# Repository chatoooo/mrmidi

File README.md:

# Mr. MIDI
MIDI interface for MiSTer FPGA with ADC to mix music with SFX and output over HDMI/audio jack. The design aims to DIY assembly and uses only thru-hole parts.

## Principe
Thanks to MT-32pi - MiSTer compatibility, there are MIDI out and I2S signals on the user port on the Analog/Digital IO board. 
MT-32pi gets the MIDI data and produces I2S data, that are mixed with SFX output from the emulated sound card.
To get the same result with a real MIDI synth, we need a line driver to get 3.3V logic of the MiSTer to 5V levels of the MIDI interface 
and ADC with I2S output to digitalize analog audio output from the synth. Connection with MiSTer is though USB 3.0 cable (male-male), the same one as for MT-32pi hat.

## Manufacture
The PCB is optimzied for JLCPCB. Use the gerber files from the latest release. 

## BOM

|Id |Value|Note|
|---|-----|----|
|R1 |180R 0207|For LED D1|
|R2 |180R 0207|For LED D2|
|R3 |4K7 0207 |signal for Q1|
|R4 |220R 0207|MIDI interface|
|R5 |220R 0207|MIDI interface|
|C1 |100nF 5mm|bypass|
|Q1 |BS170_D26Z|for driving LED D2|
|D1 |3mm 20mA 2V|power LED|
|D2 |3mm 20mA 2V|activity LED|
|U1 |SN74HCT14N||
|J1 |CONNFLY DS1095-05-LNR0|USB 3.0 A Female|
|J2 |DIN 5 Female|https://www.mouser.co.uk/ProductDetail/490-SDS-50J, or similar, almost all DIN5-180 connectors have the same footprint|
|A1 |PCM1808|ADC module|

A1 is PCM1808 module abvailable on Aliexpress: <https://www.aliexpress.com/item/1005006141604047.html>. 
There is another PCM1808 module, usually purple which is not compatible with this project.
The module can be soldered directly or using female pin headers (1x2, 1x5, 1x3).

## Bootstraping the module
The PCM1808 module needs to be set to master, I2S-24 bits, 48000Hz.
| OP1 | OP2 | OP3 |
|:---:|:---:|:---:|
|open |short|open |

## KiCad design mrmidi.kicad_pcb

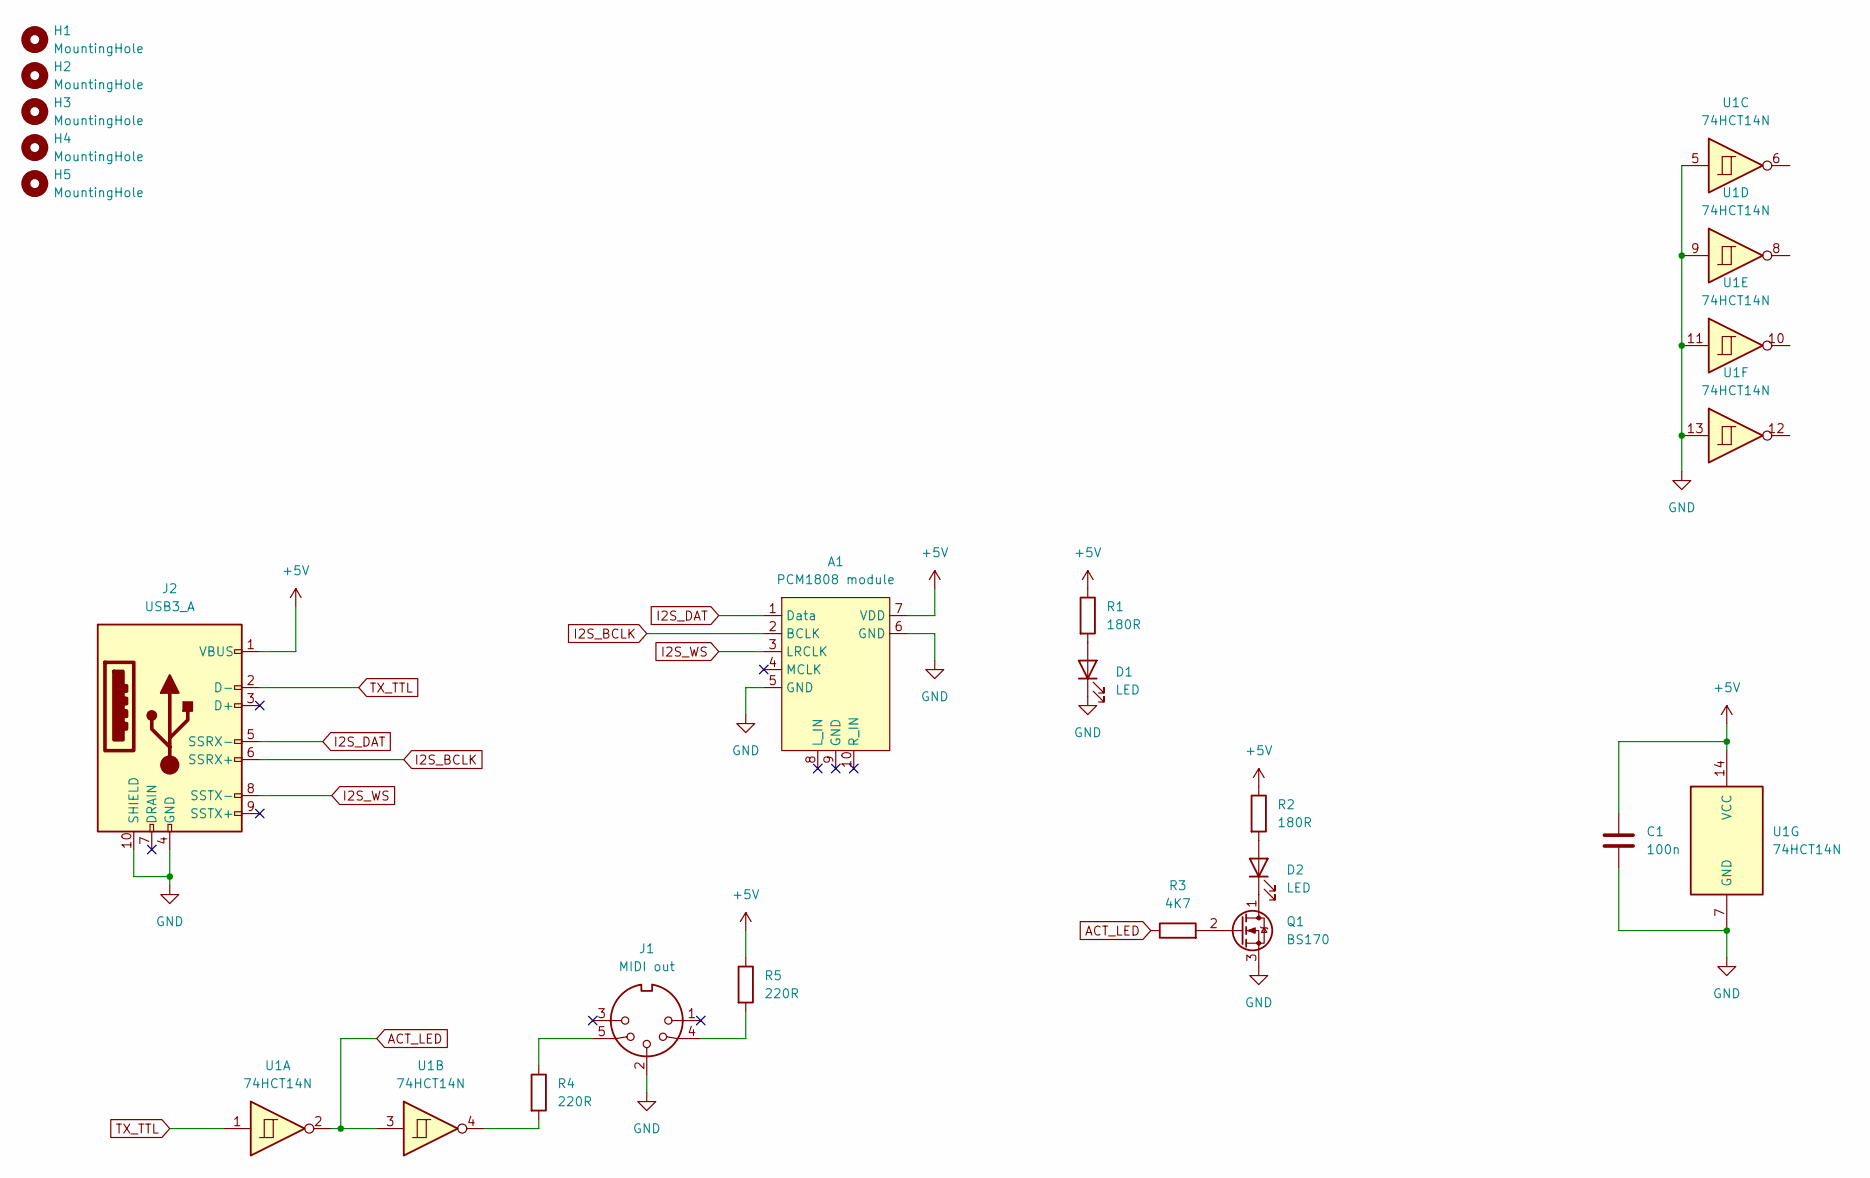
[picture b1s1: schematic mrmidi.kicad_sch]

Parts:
A1: PCM1808 module; PCM1808_module_upside_down
C1: 100n; C_Disc_D4.3mm_W1.9mm_P5.00mm
D1, D2: LED; LED_D3.0mm
H1, H2, H3, H4: MountingHole; MountingHole_3mm
H5: MountingHole; MountingHole_5mm
J1: MIDI out; DIN-5-Variable
J2: USB3_A; USB3_A_Confly_1095-05
Q1: BS170; TO-92L_Inline_Wide
R1, R2: 180R; R_Axial_DIN0207_L6.3mm_D2.5mm_P10.16mm_Horizontal
R3: 4K7; R_Axial_DIN0207_L6.3mm_D2.5mm_P10.16mm_Horizontal
R4, R5: 220R; R_Axial_DIN0207_L6.3mm_D2.5mm_P10.16mm_Horizontal
U1: 74HCT14N; DIP-14_W7.62mm

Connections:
+5V: A1.7 (VDD), C1.1, J2.1 (VBUS), R1.1, R2.1, R5.1, U1.14 (VCC)
ACT_LED: R3.1, U1.2, U1.3
GND: A1.5 (GND), A1.6 (GND), C1.2, D1.1 (K), J1.2, J2.4 (GND), J2.10 (SHIELD), Q1.3 (S), U1.5, U1.7 (GND), U1.9, U1.11, U1.13
I2S_BCLK: A1.2 (BCLK), J2.6 (SSRX+)
I2S_DAT: A1.1 (Data), J2.5 (SSRX-)
I2S_WS: A1.3 (LRCLK), J2.8 (SSTX-)
unnamed: D1.2 (A), R1.2
unnamed: D2.2 (A), R2.2
unnamed: D2.1 (K), Q1.1 (D)
unnamed: J1.4, R5.2
unnamed: J1.5, R4.1
unnamed: Q1.2 (G), R3.2
unnamed: R4.2, U1.4
TX_TTL: J2.2 (D-), U1.1

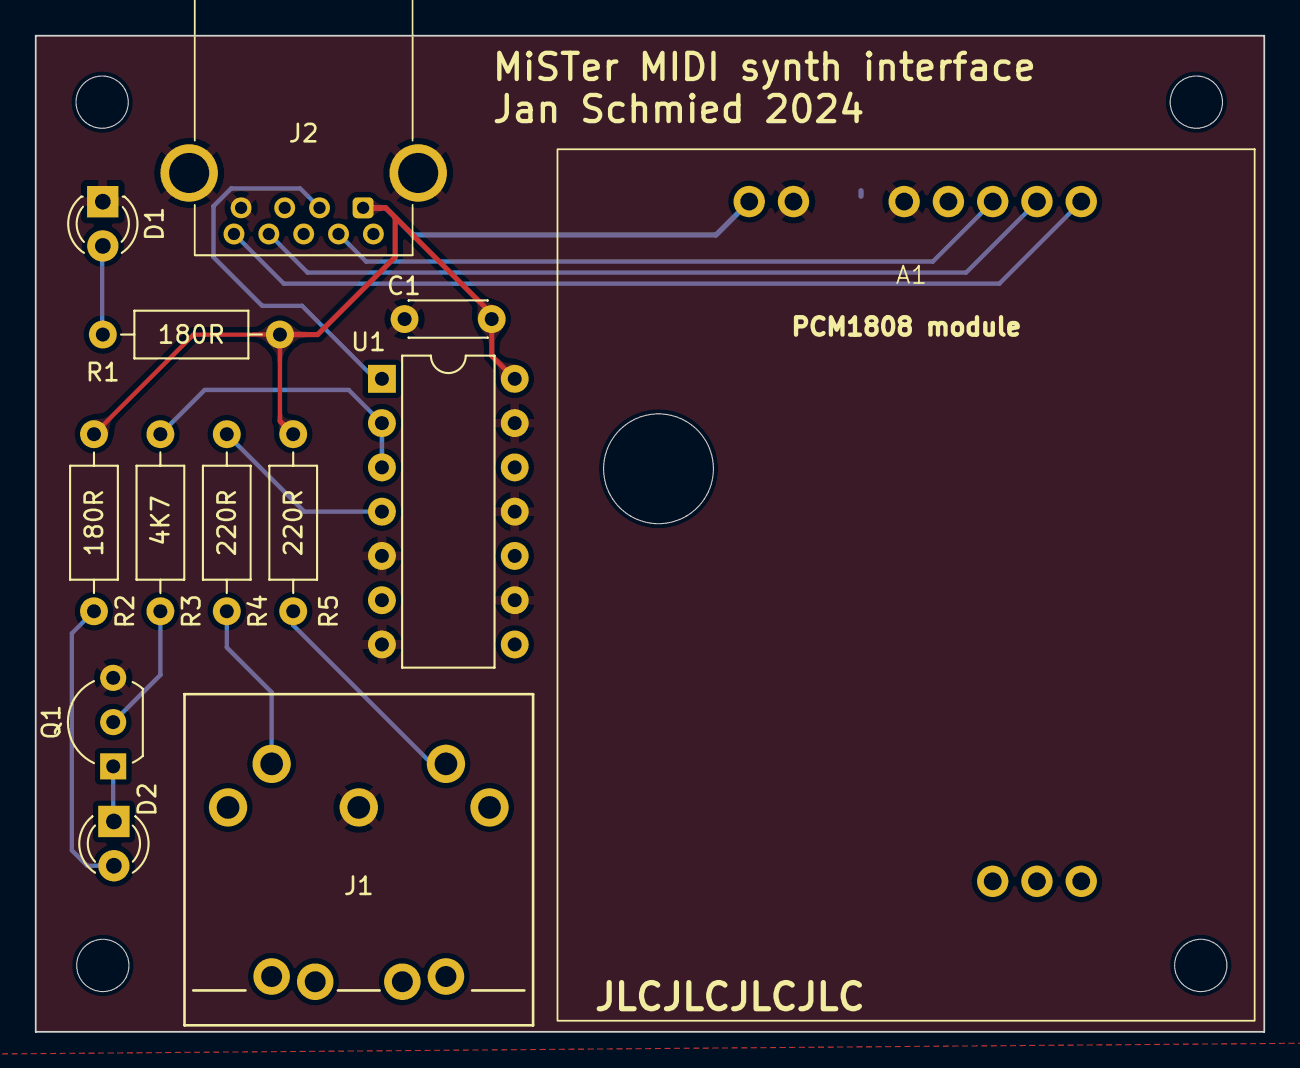
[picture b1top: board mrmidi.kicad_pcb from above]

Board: 2 copper layers, 70.5 x 57.2 mm, 18 parts (0 on the bottom side), 14 nets.

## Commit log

2024-05-21 initial files
2024-05-21 readme typo
2024-05-21 update license
2024-05-21 readme update
